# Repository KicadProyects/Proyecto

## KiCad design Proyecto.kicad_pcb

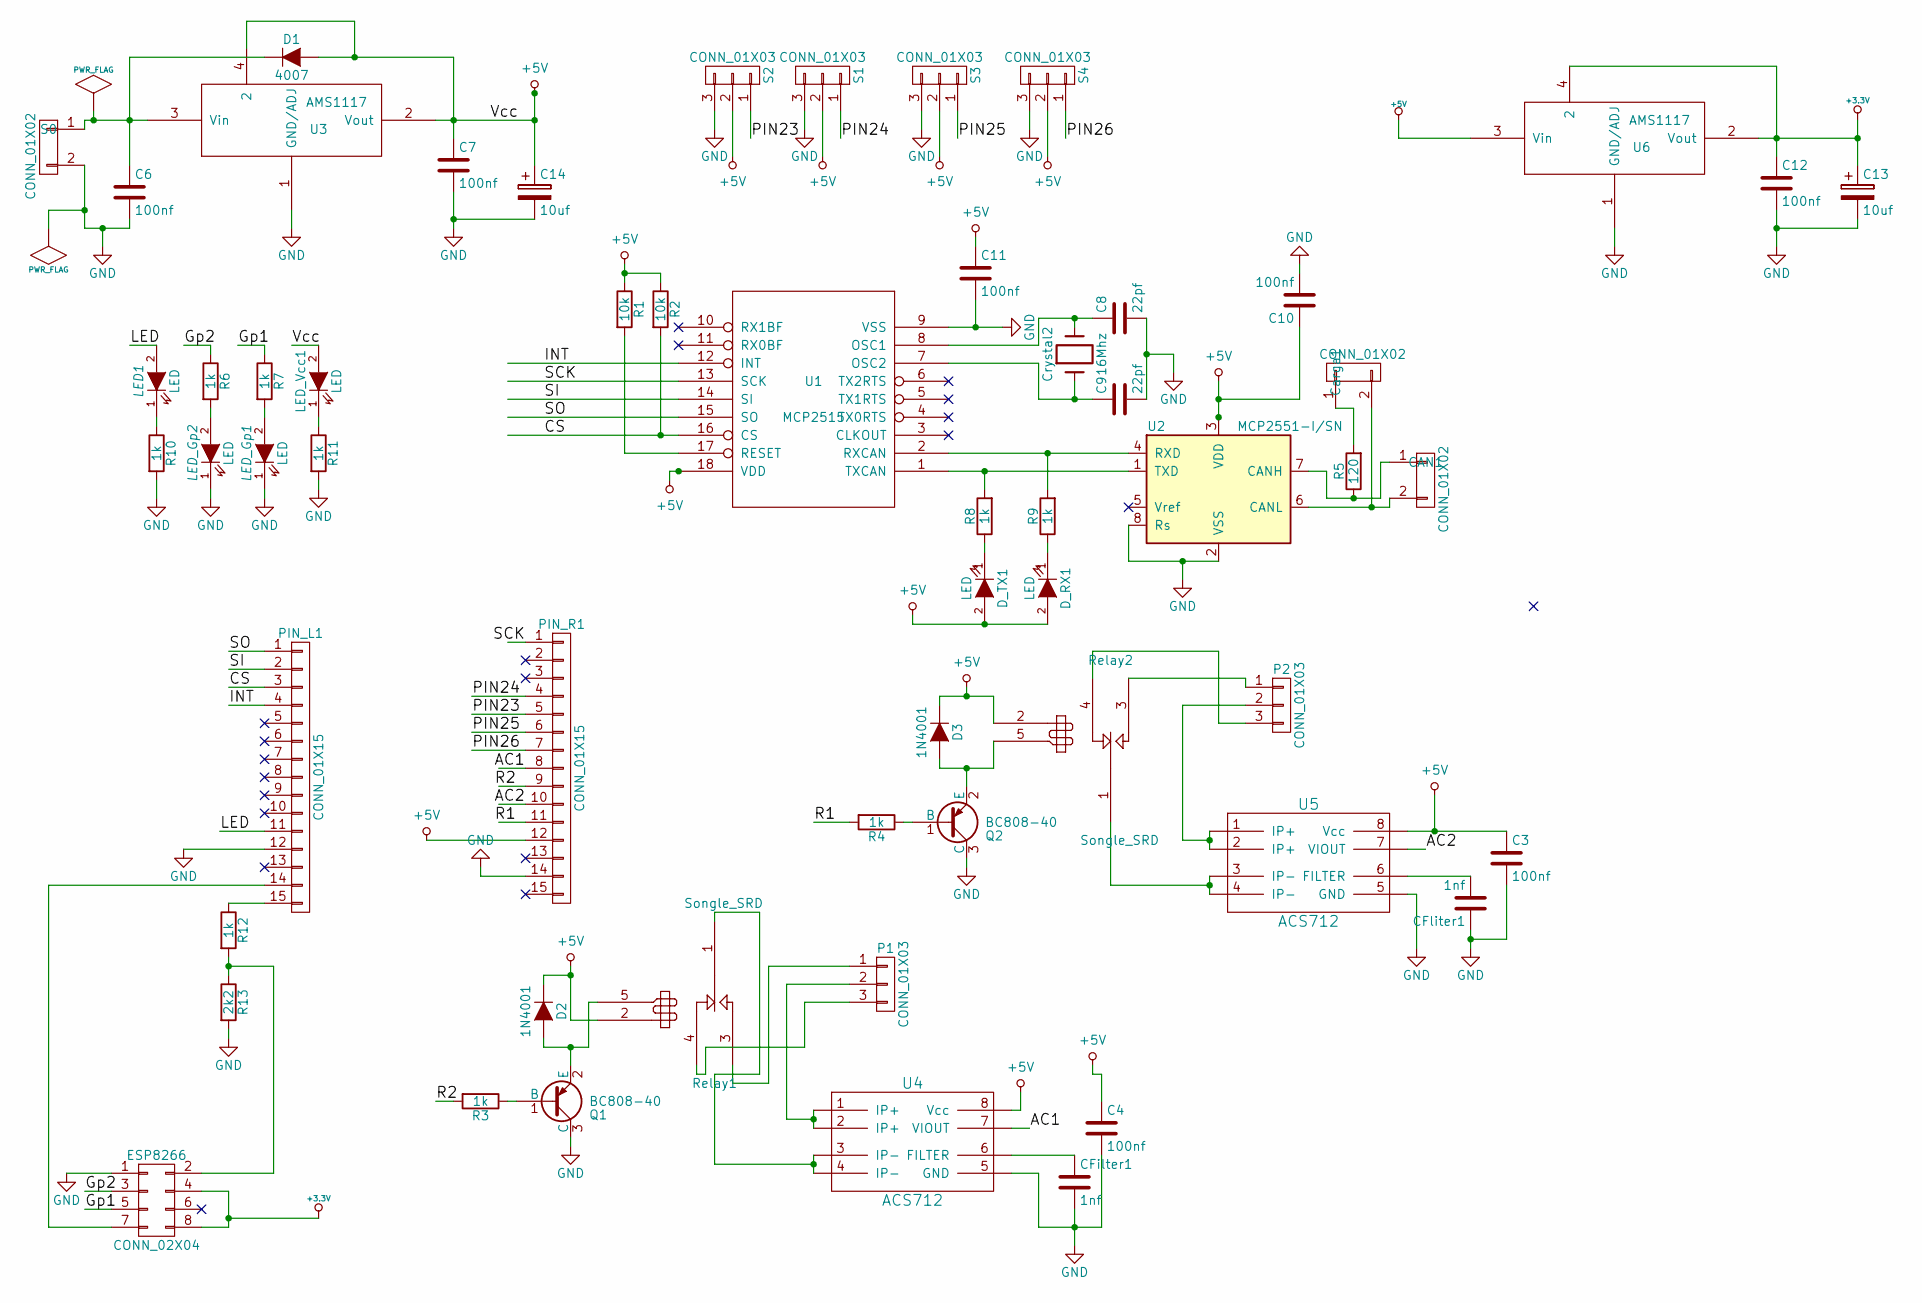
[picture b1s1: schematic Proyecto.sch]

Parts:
C3, C4, C6, C7, C10, C11, C12: 100nf; cnp_6mm_disc
C8, C9: 22pf; cnp_6mm_disc
C13, C14: 10uf; CP_5x11mm
CAN1: CONN_01X02; mkds_1,5-2
CFilter1: 1nf; cnp_6mm_disc
CFliter1: 1nf; cnp_6mm_disc
Carga1: CONN_01X02; Pin_Header_Straight_1x02
Crystal2: 16Mhz; crystal_hc-49s
D1: 4007; Diode_DO-35_SOD27_Horizontal_RM10
D2, D3: 1N4001; Diode_DO-35_SOD27_Horizontal_RM10
D_RX1: LED; LED-3MM
D_TX1: LED; LED-3MM
ESP8266: CONN_02X04; pin_socket_4x2
LED1: LED; LED-3MM
LED_Gp1, LED_Gp2: LED; LED-3MM
LED_Vcc1: LED; LED-3MM
P1, P2: CONN_01X03; mkds_1,5-3
PIN_L1: CONN_01X15; pin_socket_15
PIN_R1: CONN_01X15; pin_socket_15
Q1, Q2: BC808-40; SOT-23
R1, R2: 10k; RC05
R3, R4, R6, R7, R8, R9, R10, R11, R12: 1k; RC05
R5: 120; RC05
R13: 2k2; RC05
Relay1, Relay2: Songle_SRD; Relay_SANYOU_SRD_Series_Form_C
S0: CONN_01X02; mkds_1,5-2
S1, S2, S3, S4: CONN_01X03; Pin_Header_Straight_1x03
U1: MCP2515; SOIC-18_7.5x11.6mm_Pitch1.27mm
U2: MCP2551-I/SN; SOIC-8-N
U3, U6: AMS1117; SOT-223
U4, U5: ACS712; SOIC-8-N

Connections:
+3.3V: C12.1, C13.1, ESP8266.4, ESP8266.8, U6.2 (Vout), U6.4 (2)
+5V: C3.1, C4.1, C7.1, C10.1, C11.1, C14.1, D1.2 (A), D2.1 (K), D3.1 (K), D_RX1.2 (A), D_TX1.2 (A), LED_Vcc1.2 (A), PIN_R1.12, R1.1, R2.1, Relay1.2 (Coil), Relay2.2 (Coil), S1.2, S2.2, S3.2, S4.2, U1.18 (VDD), U2.3 (VDD), U3.2 (Vout), U3.4 (2), U4.8 (Vcc), U5.8 (Vcc), U6.3 (Vin)
/AC1: PIN_R1.8, U4.7 (VIOUT)
/AC2: PIN_R1.10, U5.7 (VIOUT)
/CS: PIN_L1.3, R2.2, U1.16 (CS)
/Gp1: ESP8266.5, R7.1
/Gp2: ESP8266.3, R6.1
/INT: PIN_L1.4, U1.12 (INT)
/LED: LED1.2 (A), PIN_L1.11
/PIN23: PIN_R1.5, S2.1
/PIN24: PIN_R1.4, S1.1
/PIN25: PIN_R1.6, S3.1
/PIN26: PIN_R1.7, S4.1
/R1: PIN_R1.11, R4.2
/R2: PIN_R1.9, R3.2
/SCK: PIN_R1.1, U1.13 (SCK)
/SI: PIN_L1.2, U1.14 (SI)
/SO: PIN_L1.1, U1.15 (SO)
GND: C3.2, C4.2, C6.2, C7.2, C8.2, C9.2, C10.2, C11.2, C12.2, C13.2, C14.2, CFilter1.2, CFliter1.1, ESP8266.1, LED_Gp1.1 (K), LED_Gp2.1 (K), PIN_L1.12, PIN_R1.14, Q1.3 (C), Q2.3 (C), R10.2, R11.2, R13.2, S0.2, S1.3, S2.3, S3.3, S4.3, U1.9 (VSS), U2.2 (VSS), U2.8 (Rs), U3.1 (GND/ADJ), U4.5 (GND), U5.5 (GND), U6.1 (GND/ADJ)
unnamed: C6.1, D1.1 (K), S0.1, U3.3 (Vin)
unnamed: C8.1, Crystal2.2, U1.8 (OSC1)
unnamed: C9.1, Crystal2.1, U1.7 (OSC2)
unnamed: CAN1.1, R5.1, U2.7 (CANH)
unnamed: CAN1.2, Carga1.2, U2.6 (CANL)
unnamed: CFilter1.1, U4.6 (FILTER)
unnamed: CFliter1.2, U5.6 (FILTER)
unnamed: Carga1.1, R5.2
unnamed: D2.2 (A), Q1.2 (E), Relay1.5 (Coil)
unnamed: D3.2 (A), Q2.2 (E), Relay2.5 (Coil)
unnamed: D_RX1.1 (K), R9.1
unnamed: D_TX1.1 (K), R8.1
unnamed: ESP8266.2, R12.2, R13.1
unnamed: ESP8266.7, PIN_L1.14
unnamed: LED1.1 (K), R10.1
unnamed: LED_Gp1.2 (A), R7.2
unnamed: LED_Gp2.2 (A), R6.2
unnamed: LED_Vcc1.1 (K), R11.1
unnamed: P1.1, Relay1.3 (NO)
unnamed: P1.2, U4.1 (IP+), U4.2 (IP+)
unnamed: P1.3, Relay1.4 (NC)
unnamed: P2.1, Relay2.3 (NO)
unnamed: P2.2, U5.1 (IP+), U5.2 (IP+)
unnamed: P2.3, Relay2.4 (NC)
unnamed: PIN_L1.15, R12.1
unnamed: Q1.1 (B), R3.1
unnamed: Q2.1 (B), R4.1
unnamed: R1.2, U1.17 (RESET)
unnamed: R8.2, U1.1 (TXCAN), U2.1 (TXD)
unnamed: R9.2, U1.2 (RXCAN), U2.4 (RXD)
unnamed: Relay1.1 (C), U4.3 (IP-), U4.4 (IP-)
unnamed: Relay2.1 (C), U5.3 (IP-), U5.4 (IP-)

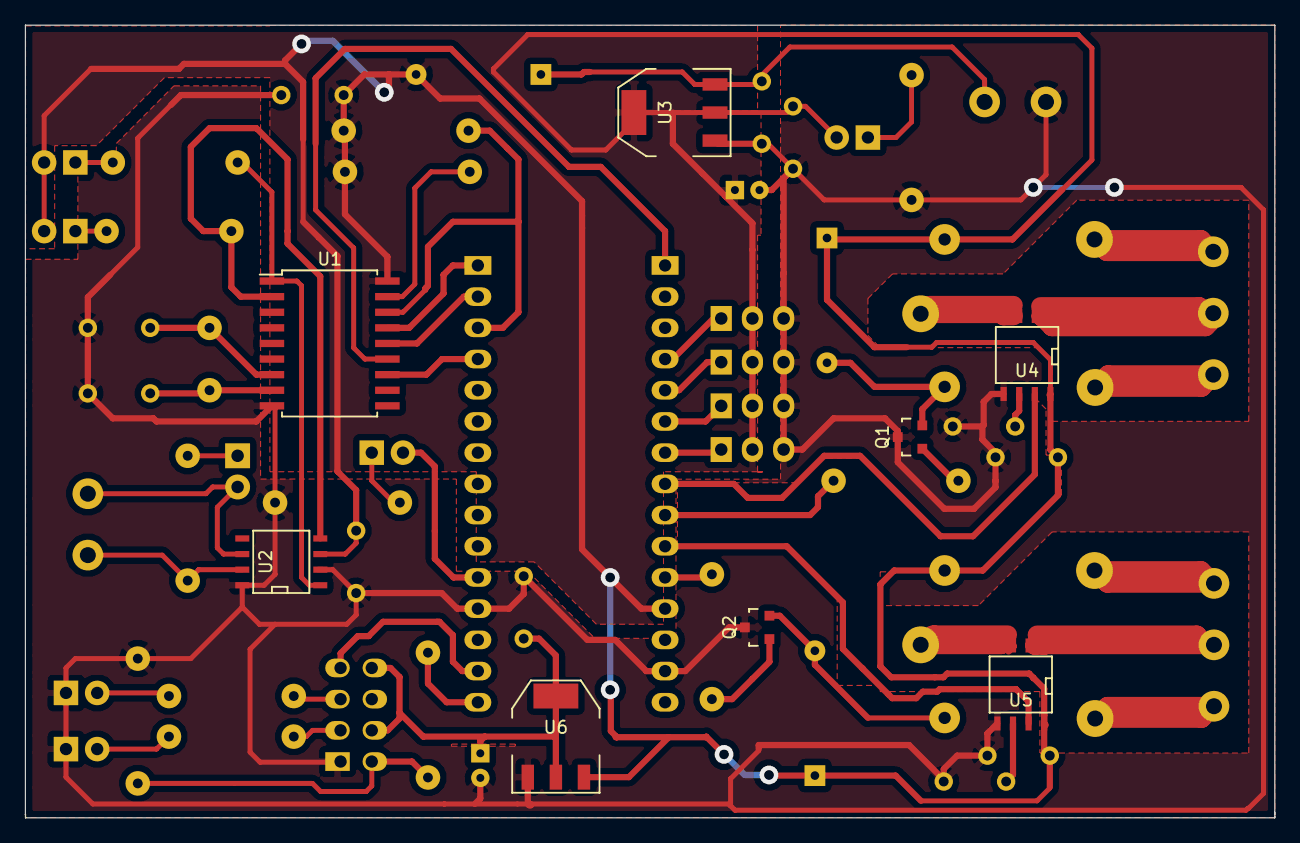
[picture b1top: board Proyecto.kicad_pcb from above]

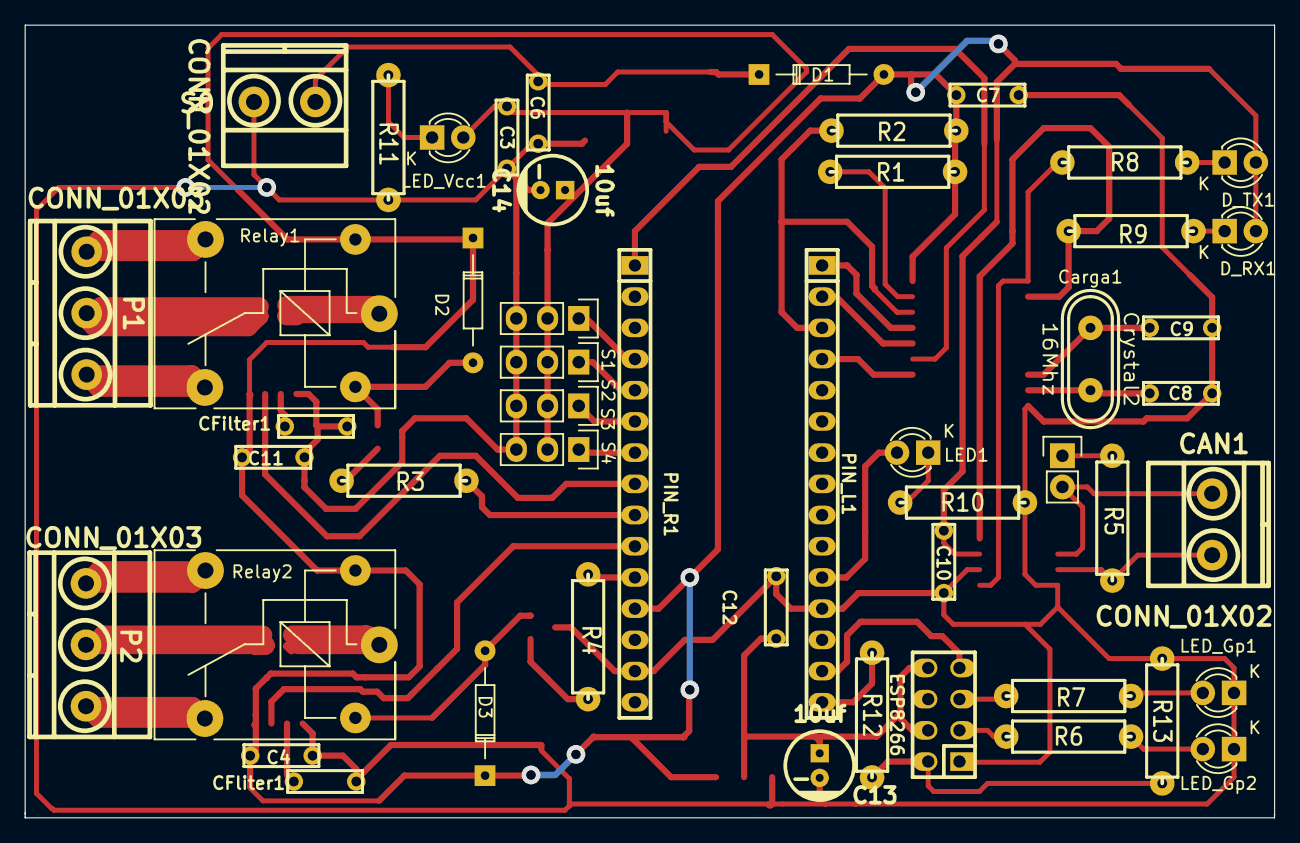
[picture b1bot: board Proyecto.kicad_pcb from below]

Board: 2 copper layers, 101.7 x 64.5 mm, 58 parts (50 on the bottom side), 51 nets.

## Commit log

2016-06-22 :octocat: Added .gitattributes & .gitignore files
2016-06-23 add componenets
2016-06-24 fix
    se quito el micro y se coloco pines hembra para insertar NanoArduino en
    placa
2016-06-24 fix pcb
2016-06-29 fix terrena
2016-07-01 fix casa
    se dieron vuelta los pines del nano arudino
2016-07-05 fix tamaños y nuevas librerias
2016-07-05 foto
2016-07-06 fix pcb casa
2016-07-06 fisx
    con 4 puentes... 6.6 cm x12 cm
2016-07-07 fix
    achicamiento 6.5 x 10.7 cm
2016-07-11 plano de masa
2016-07-12 casa
2016-07-12 full ok
